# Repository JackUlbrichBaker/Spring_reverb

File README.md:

Hello! This is a "simple" spring reverb using a high current op amp to drive a ~600ohm impedance spring reverb with ~4.5mA of current.  The signal path is entirely analog and uses jfets to emulate that smooth TUUUUUUbe sound for guitar purists.
Almost entirely so I have cheap reverb on my amp and so I can show off I know how to design analog circuits when I apply for jobs.

PCB Routing:

PCB render:

Actual PCB:
TODO

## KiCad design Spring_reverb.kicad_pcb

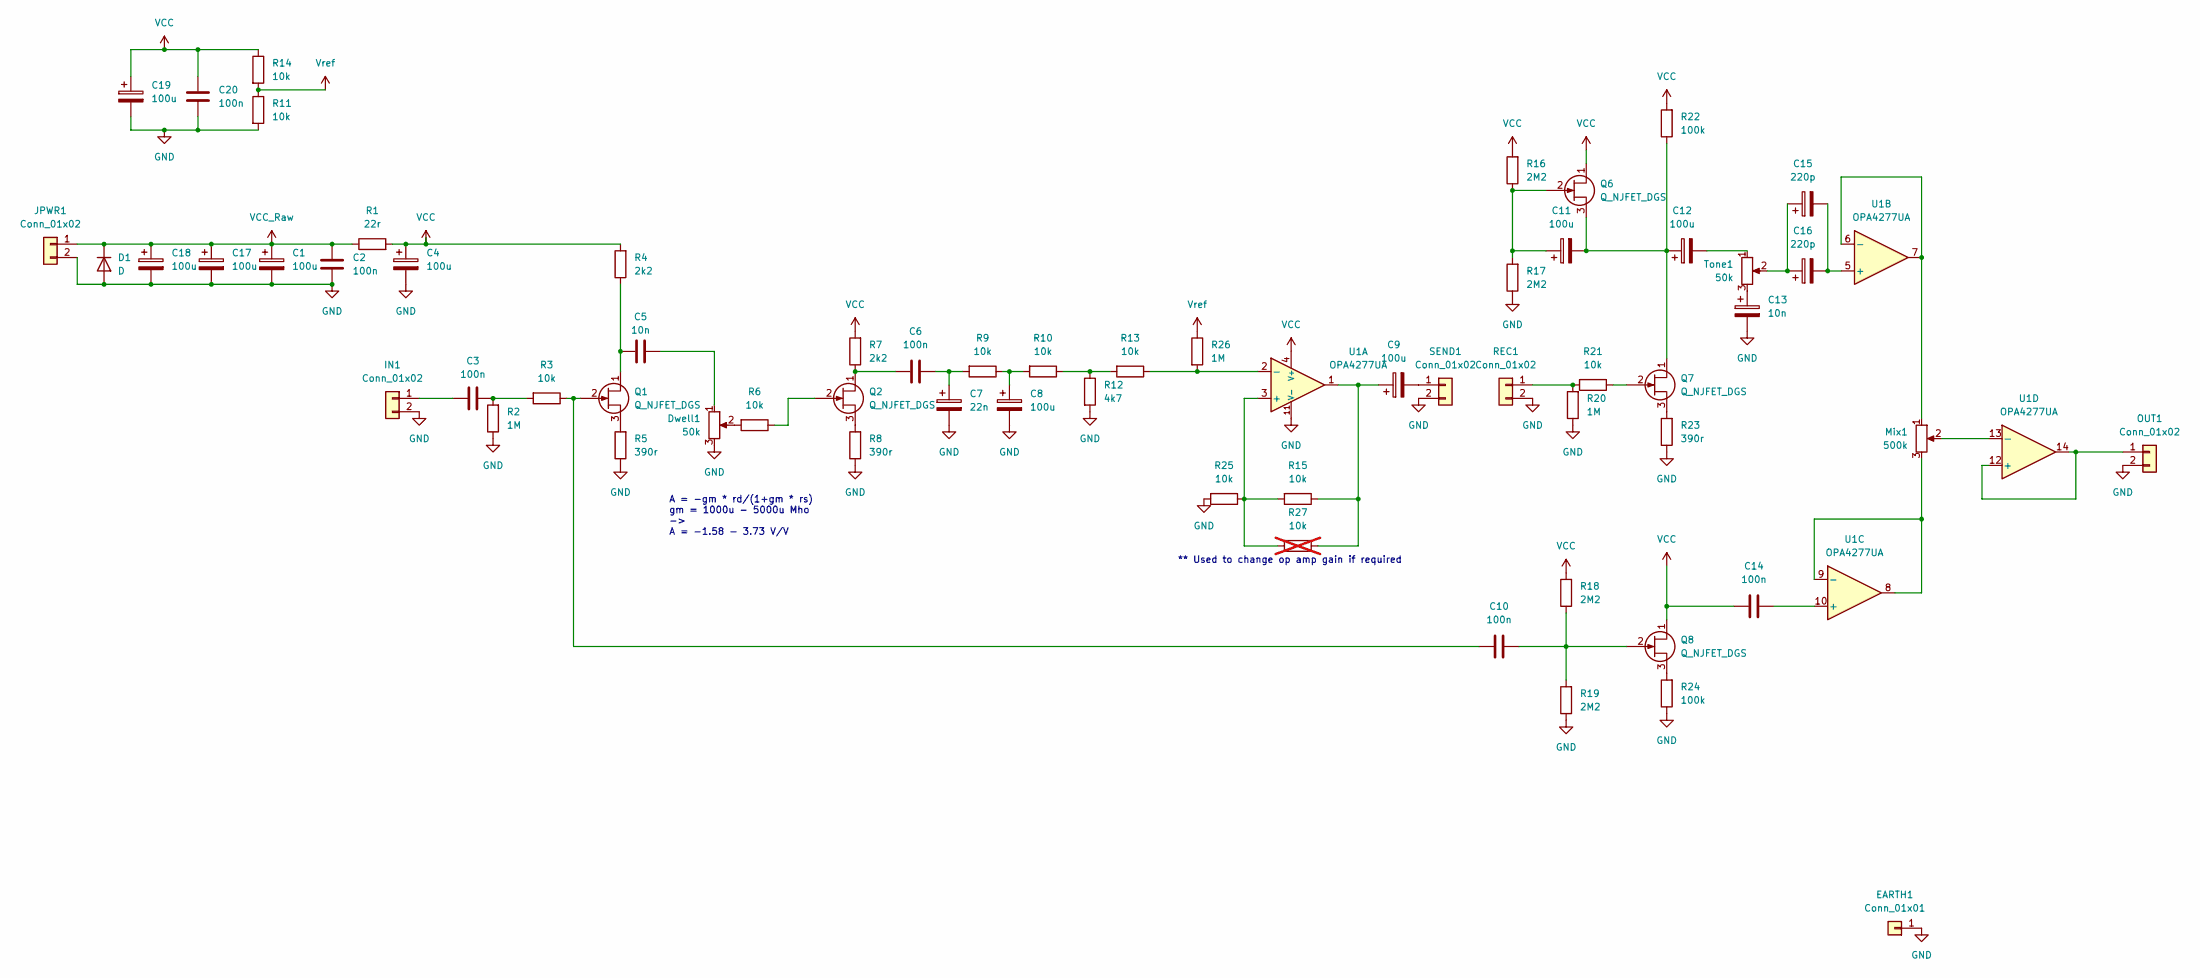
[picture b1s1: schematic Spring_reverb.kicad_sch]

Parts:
C1, C4, C8, C9, C11, C12, C17, C18, C19: 100u; C_0805_2012Metric_Pad1.18x1.45mm_HandSolder
C2, C3, C6, C10, C14, C20: 100n; C_0805_2012Metric_Pad1.18x1.45mm_HandSolder
C5, C13: 10n; C_0805_2012Metric_Pad1.18x1.45mm_HandSolder
C7: 22n; C_0805_2012Metric_Pad1.18x1.45mm_HandSolder
C15, C16: 220p; C_0805_2012Metric_Pad1.18x1.45mm_HandSolder
D1: D; C_0805_2012Metric_Pad1.18x1.45mm_HandSolder
Dwell1: 50k; Pot_16mm_NoDet_RV16AF-4A
EARTH1: Conn_01x01; PinHeader_1x01_P2.54mm_Vertical
IN1: Conn_01x02; PinSocket_1x02_P2.54mm_Vertical; Part Number 1-0201FBV0T
JPWR1: Conn_01x02; PinSocket_1x02_P2.54mm_Vertical; Part Number 1-0201FBV0T
Mix1: 500k; Pot_16mm_NoDet_RV16AF-4A
OUT1: Conn_01x02; PinSocket_1x02_P2.54mm_Vertical; Part Number 1-0201FBV0T
Q1, Q2, Q6, Q7, Q8: Q_NJFET_DGS; SOT-23
R1: 22r; R_0815_2038Metric_Pad1.20x4.05mm_HandSolder
R2, R20, R26: 1M; R_0815_2038Metric_Pad1.20x4.05mm_HandSolder
R3, R6, R9, R10, R11, R13, R14, R15, R21, R25: 10k; R_0815_2038Metric_Pad1.20x4.05mm_HandSolder
R4, R7: 2k2; R_0815_2038Metric_Pad1.20x4.05mm_HandSolder
R5, R8, R23: 390r; R_0815_2038Metric_Pad1.20x4.05mm_HandSolder
R12: 4k7; R_0815_2038Metric_Pad1.20x4.05mm_HandSolder
R16, R17, R18, R19: 2M2; R_0815_2038Metric_Pad1.20x4.05mm_HandSolder
R22, R24: 100k; R_0815_2038Metric_Pad1.20x4.05mm_HandSolder
R27: 10k; R_0815_2038Metric_Pad1.20x4.05mm_HandSolder; not fitted
REC1: Conn_01x02; PinSocket_1x02_P2.54mm_Vertical; Part Number 1-0201FBV0T
SEND1: Conn_01x02; PinSocket_1x02_P2.54mm_Vertical; Part Number 1-0201FBV0T
Tone1: 50k; Pot_16mm_NoDet_RV16AF-4A
U1: OPA4277UA; SOIC-14_3.9x8.7mm_P1.27mm

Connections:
GND: C1.2, C2.2, C4.2, C7.2, C8.2, C13.2, C17.2, C18.2, C19.2, C20.2, D1.2 (A), Dwell1.3, EARTH1.1, IN1.2, JPWR1.2, OUT1.2, R2.1, R5.1, R8.1, R11.2, R12.2, R17.1, R19.1, R20.1, R23.1, R24.1, R25.2, REC1.2, SEND1.2, U1.11 (V-)
unnamed: C3.2, R2.2, R3.2
unnamed: C5.2, Dwell1.1
unnamed: C6.2, C7.1, R9.2
unnamed: C8.1, R9.1, R10.2
unnamed: C9.1, R15.1, R27.1, U1.1
unnamed: C12.2, Tone1.1
unnamed: C13.1, Tone1.3
unnamed: C15.1, C16.1, Tone1.2
unnamed: Dwell1.2, R6.2
unnamed: C3.1, IN1.1
unnamed: OUT1.1, U1.12 (+), U1.14
unnamed: C5.1, Q1.1 (D), R4.1
unnamed: C10.1, Q1.2 (G), R3.1
unnamed: Q1.3 (S), R5.2
unnamed: C6.1, Q2.1 (D), R7.1
unnamed: Q2.2 (G), R6.1
unnamed: Q2.3 (S), R8.2
unnamed: C11.1, Q6.2 (G), R16.1, R17.2
unnamed: C11.2, C12.1, Q6.3 (S), Q7.1 (D), R22.1
unnamed: Q7.2 (G), R21.1
unnamed: Q7.3 (S), R23.2
unnamed: C10.2, Q8.2 (G), R18.1, R19.2
unnamed: Q8.3 (S), R24.2
unnamed: R10.1, R12.1, R13.2
unnamed: R20.2, R21.2, REC1.1
unnamed: C9.2, SEND1.1
unnamed: R15.2, R25.1, R27.2, U1.3 (+)
unnamed: R13.1, R26.2, U1.2 (-)
unnamed: C15.2, C16.2, U1.5 (+)
unnamed: Mix1.1, U1.6 (-), U1.7
unnamed: C14.2, U1.10 (+)
unnamed: Mix1.3, U1.8, U1.9 (-)
unnamed: Mix1.2, U1.13 (-)
VCC: C4.1, C14.1, C19.1, C20.1, Q6.1 (D), Q8.1 (D), R1.2, R4.2, R7.2, R14.1, R16.2, R18.2, R22.2, U1.4 (V+)
VCC_Raw: C1.1, C2.1, C17.1, C18.1, D1.1 (K), JPWR1.1, R1.1
Vref: R11.1, R14.2, R26.1

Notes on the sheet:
** Used to change op amp gain if required
A = -gm * rd/(1+gm * rs) gm = 1000u - 5000u Mho -> A = -1.58 - 3.73 V/V

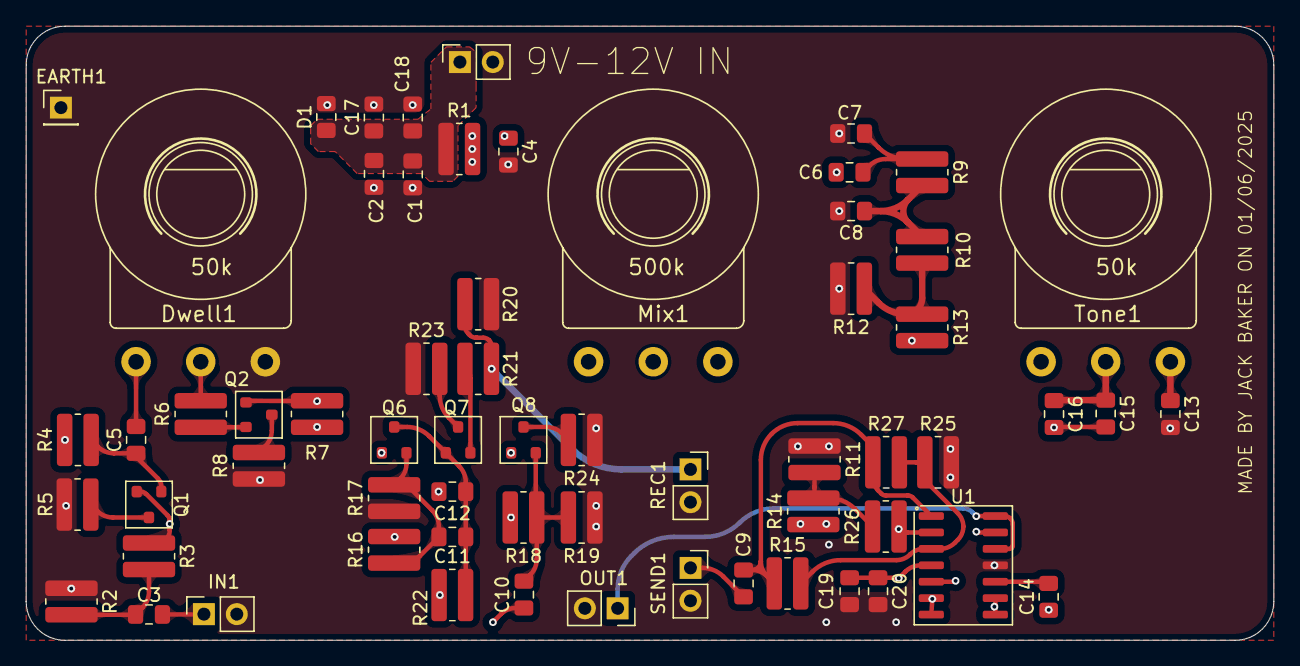
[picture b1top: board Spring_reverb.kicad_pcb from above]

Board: 4 copper layers, 96.5 x 47.5 mm, 63 parts (0 on the bottom side), 37 nets.

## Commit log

2025-07-02 init
2025-07-02 dump init
